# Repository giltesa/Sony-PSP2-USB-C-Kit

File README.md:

# Sony PSP 2 USB-C Kit

The **Sony PSP 2: USB-C Kit** is a board that allows to replace the original charging connector for a modern and standard **USB-C**.

**If your original connector is too old or damaged** and you need a new one, or **if you would like to charge your Sony PSP with a standard USB-C charger**, like the charger of your phone, laptop, you can with this board.

This board is compatible with these models:

*   Sony PSP 2000
*   Sony PSP 3000

## Would you like it?

https://shop.giltesa.com/product/sony-psp-2000-3000-usb-c-kit/

## More

- [giltesa.com](https://giltesa.com "giltesa.com")
- [twitter.com](https://twitter.com/giltesa "twitter.com")

## License

This project is licensed under a **Creative Commons** license:
**[Attribution-NonCommercial-ShareAlike 4.0 International (CC BY-NC-SA 4.0) ](https://creativecommons.org/licenses/by-nc-sa/4.0/)**

Check the [LICENSE.md](LICENSE.md) for more information.

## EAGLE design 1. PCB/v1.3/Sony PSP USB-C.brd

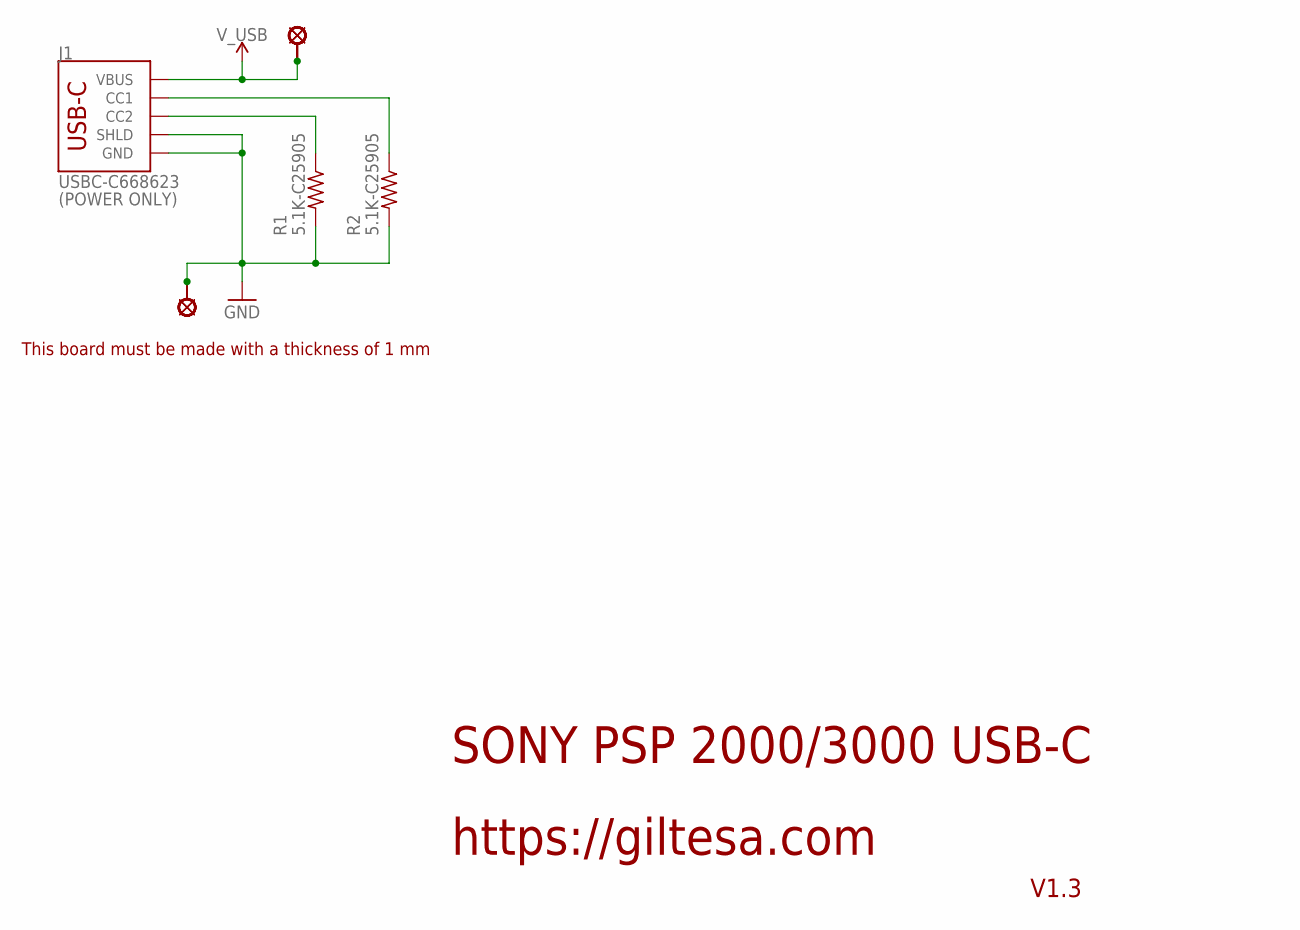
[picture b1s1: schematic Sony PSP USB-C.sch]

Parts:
J1: USBC-C668623; USB-C_6P
R1, R2: 5.1K-C25905; R0402
U$1, U$2, U$3, U$4: SOLDER_PAD_N3DS; N3DS_TPAD

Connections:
GND: J1.A12-GND (GND), J1.B12-GND (GND), J1.SHLD1 (SHLD), J1.SHLD2 (SHLD), J1.SHLD3 (SHLD), J1.SHLD4 (SHLD), R1.2, R2.2, U$1.1, U$4.1
unnamed: J1.B5 (CC2), R1.1
unnamed: J1.A5 (CC1), R2.1
V_USB: J1.A9-VBUS (VBUS), J1.B9-VBUS (VBUS), U$2.1, U$3.1

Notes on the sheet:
SONY PSP 2000/3000 USB-C
https://giltesa.com
V1.3
This board must be made with a thickness of 1 mm
(POWER ONLY)

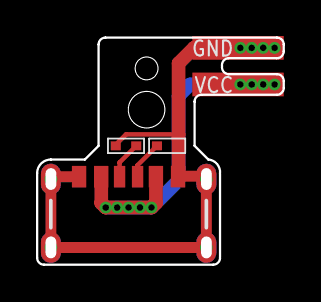
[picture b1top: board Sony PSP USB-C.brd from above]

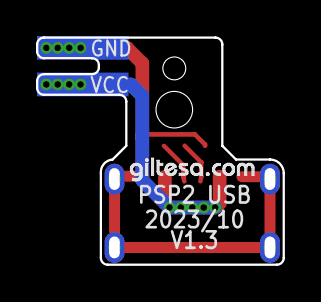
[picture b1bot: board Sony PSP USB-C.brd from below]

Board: 2 copper layers, 13.2 x 12.1 mm, 8 parts (3 on the bottom side), 4 nets.

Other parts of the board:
U$11: GILTESA.COM_MASK_7MM

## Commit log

2023-08-02 no message
2023-08-16 Added installation guide
2024-01-15 v1.2
2024-01-15 v1.3

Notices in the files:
parts and their libraries:
SparkFun: Licensing: CC v3.0 Share-Alike You are welcome to use this library for commercial purposes.
SparkFun-PowerSymbols: Licensing: Creative Commons ShareAlike 4.0 International - https://creativecommons.org/licenses/by-sa/4.0
